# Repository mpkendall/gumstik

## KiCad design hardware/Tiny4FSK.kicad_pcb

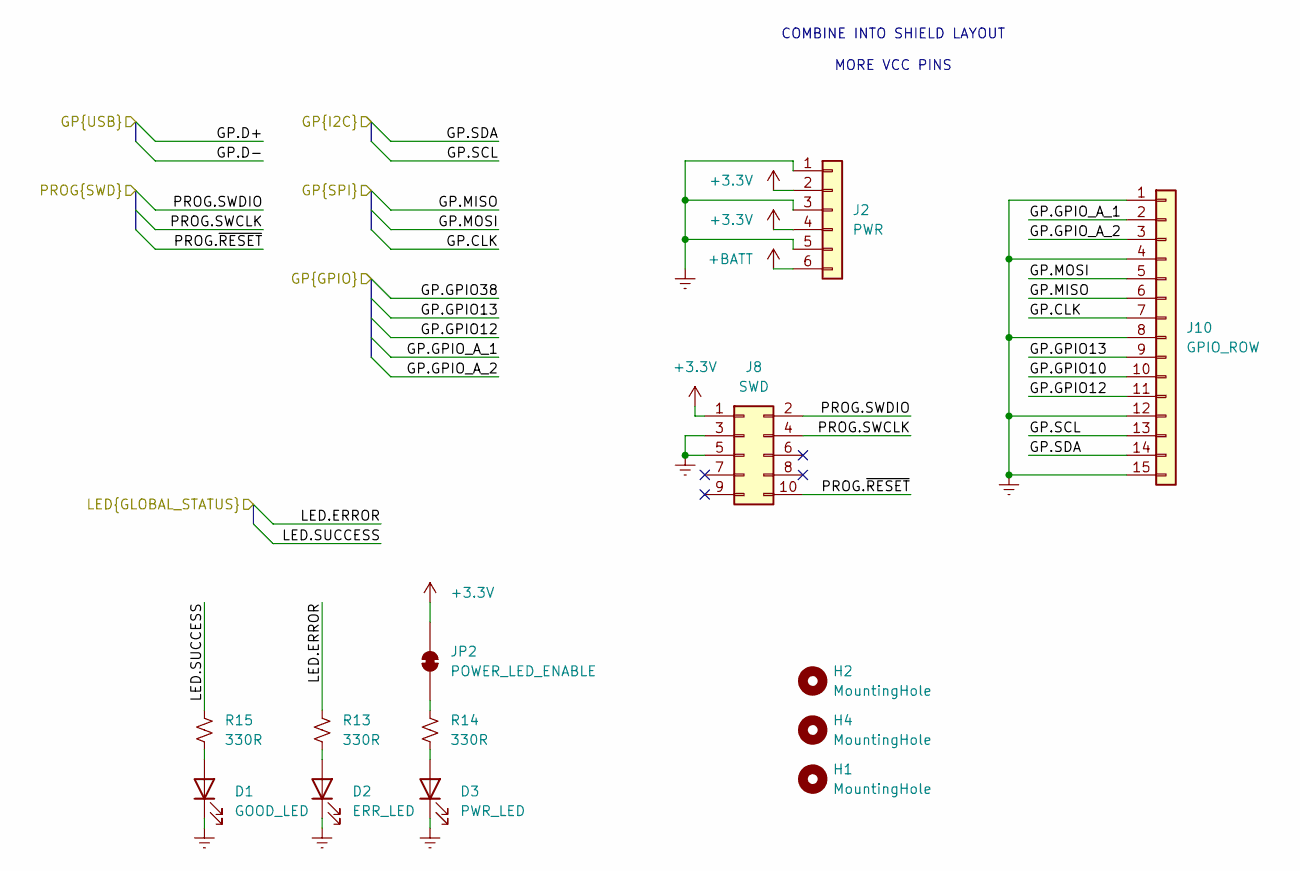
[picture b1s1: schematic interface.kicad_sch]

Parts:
D1: GOOD_LED; LED_0603_1608Metric; LCSC C2297
D2: ERR_LED; LED_0603_1608Metric; LCSC C84256
D3: PWR_LED; LED_0603_1608Metric; LCSC C84256
H1, H2, H4: MountingHole; MountingHole_2.2mm_M2
J2: PWR; PinHeader_1x06_P2.54mm_Vertical
J8: SWD; Pogo_2x05_P1.27mm
J10: GPIO_ROW; PinHeader_1x15_P2.54mm_Vertical
JP2: POWER_LED_ENABLE; SolderJumper-2_P1.3mm_Bridged_RoundedPad1.0x1.5mm
R13, R14, R15: 330R; C_0402_1005Metric; LCSC C23138

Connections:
+3.3V: J2.2, J2.4, J8.1, JP2.2 (B); also elsewhere on the board
+BATT: J2.6; also elsewhere on the board
/interface/GP.CLK: J10.7; also elsewhere on the board
/interface/GP.GPIO10: J10.10; also elsewhere on the board
/interface/GP.GPIO12: J10.11; also elsewhere on the board
/interface/GP.GPIO13: J10.9; also elsewhere on the board
/interface/GP.GPIO_A_1: J10.2; also elsewhere on the board
/interface/GP.GPIO_A_2: J10.3; also elsewhere on the board
/interface/GP.MISO: J10.6; also elsewhere on the board
/interface/GP.MOSI: J10.5; also elsewhere on the board
/interface/GP.SCL: J10.13; also elsewhere on the board
/interface/GP.SDA: J10.14; also elsewhere on the board
/interface/LED.ERROR: R13.1; also elsewhere on the board
/interface/LED.SUCCESS: R15.1; also elsewhere on the board
/interface/PROG.SWCLK: J8.4; also elsewhere on the board
/interface/PROG.SWDIO: J8.2; also elsewhere on the board
/interface/PROG.~RESET: J8.10; also elsewhere on the board
Earth: D1.1 (K), D2.1 (K), D3.1 (K), J2.1, J2.3, J2.5, J8.3, J8.5, J10.1, J10.4, J10.8, J10.12, J10.15; also elsewhere on the board
unnamed: D1.2 (A), R15.2
unnamed: D2.2 (A), R13.2
unnamed: D3.2 (A), R14.2
unnamed: JP2.1 (A), R14.1

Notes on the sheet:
COMBINE INTO SHIELD LAYOUT MORE VCC PINS

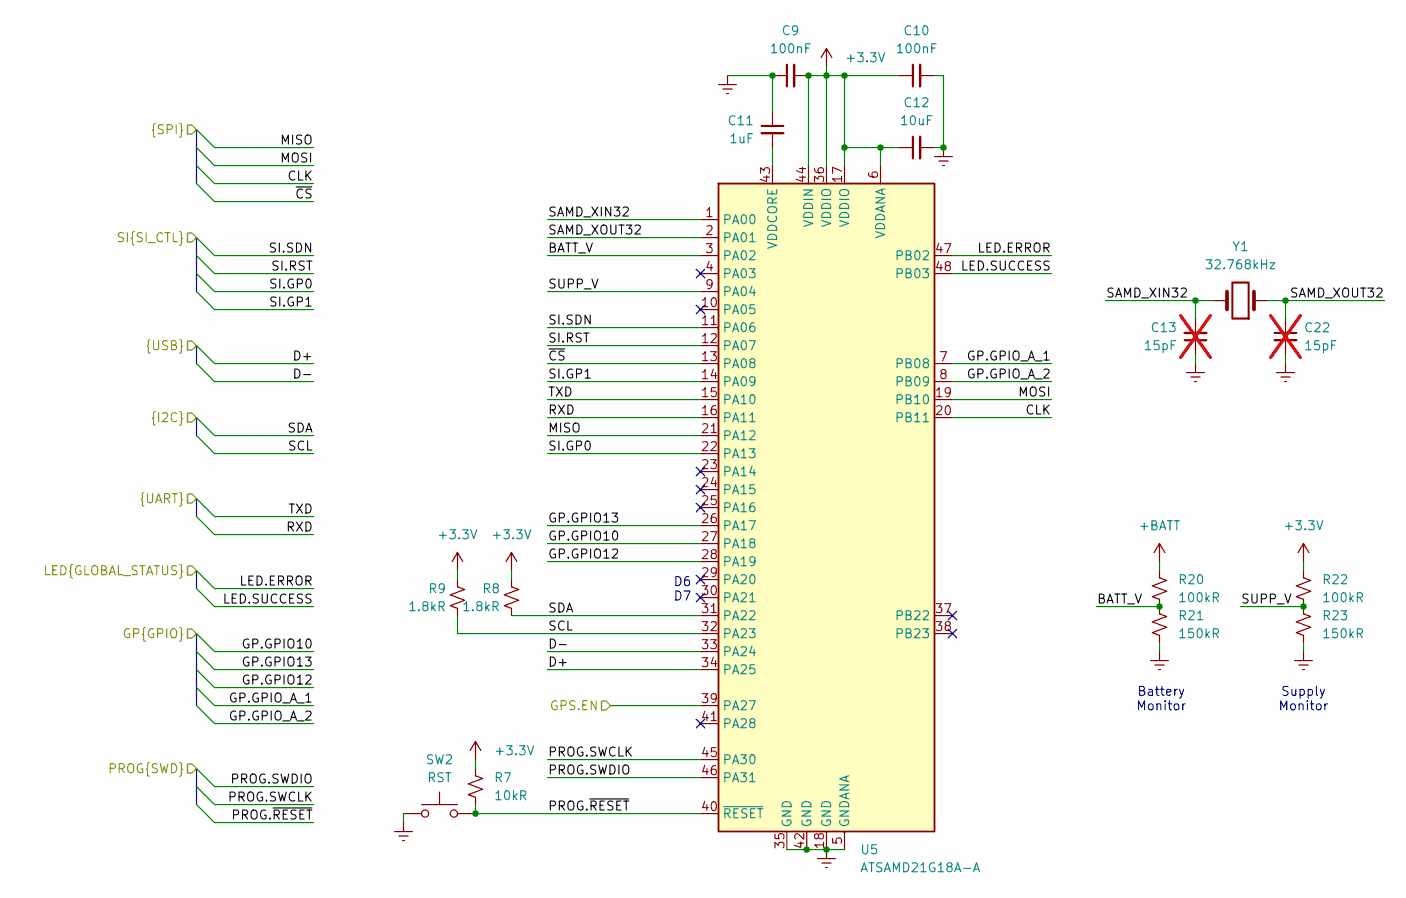
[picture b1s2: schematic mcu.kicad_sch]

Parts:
C9, C10: 100nF; C_0402_1005Metric; LCSC C1525
C11: 1uF; C_0402_1005Metric; LCSC C52923
C12: 10uF; C_0402_1005Metric; LCSC C19702
C13, C22: 15pF; C_0402_1005Metric; LCSC C1525; not fitted
R7: 10kR; R_0402_1005Metric; LCSC C25091
R8, R9: 1.8kR; R_0402_1005Metric; LCSC C4177
R20, R22: 100kR; C_0402_1005Metric; LCSC C26083
R21, R23: 150kR; C_0402_1005Metric; LCSC C26083
SW2: RST; SW_SPST_TS-1088-xR020; LCSC C2888954
U5: ATSAMD21G18A-A; TQFP-48_7x7mm_P0.5mm; LCSC C78624
Y1: 32.768kHz; Crystal_SMD_3215-2Pin_3.2x1.5mm; LCSC C32346

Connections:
+3.3V: C9.2, C10.1, C12.1, R7.2, R8.1, R9.1, R22.1, U5.6 (VDDANA), U5.17 (VDDIO), U5.36 (VDDIO), U5.44 (VDDIN); also elsewhere on the board
+BATT: R20.1; also elsewhere on the board
/interface/GP.CLK: U5.20 (PB11); also elsewhere on the board
/interface/GP.D+: U5.34 (PA25); also elsewhere on the board
/interface/GP.D-: U5.33 (PA24); also elsewhere on the board
/interface/GP.GPIO10: U5.27 (PA18); also elsewhere on the board
/interface/GP.GPIO12: U5.28 (PA19); also elsewhere on the board
/interface/GP.GPIO13: U5.26 (PA17); also elsewhere on the board
/interface/GP.GPIO_A_1: U5.7 (PB08); also elsewhere on the board
/interface/GP.GPIO_A_2: U5.8 (PB09); also elsewhere on the board
/interface/GP.MISO: U5.21 (PA12); also elsewhere on the board
/interface/GP.MOSI: U5.19 (PB10); also elsewhere on the board
/interface/GP.SCL: R9.2, U5.32 (PA23); also elsewhere on the board
/interface/GP.SDA: R8.2, U5.31 (PA22); also elsewhere on the board
/interface/GP.~CS: U5.13 (PA08); also elsewhere on the board
/interface/LED.ERROR: U5.47 (PB02); also elsewhere on the board
/interface/LED.SUCCESS: U5.48 (PB03); also elsewhere on the board
/interface/PROG.SWCLK: U5.45 (PA30); also elsewhere on the board
/interface/PROG.SWDIO: U5.46 (PA31); also elsewhere on the board
/interface/PROG.~RESET: R7.1, SW2.2, U5.40 (~RESET); also elsewhere on the board
/mcu/BATT_V: R20.2, R21.1, U5.3 (PA02)
/mcu/GPS.EN: U5.39 (PA27); also elsewhere on the board
/mcu/RXD: U5.16 (PA11); also elsewhere on the board
/mcu/SAMD_XIN32: C13.2, U5.1 (PA00), Y1.2
/mcu/SAMD_XOUT32: C22.1, U5.2 (PA01), Y1.1
/mcu/SI.GP0: U5.22 (PA13); also elsewhere on the board
/mcu/SI.GP1: U5.14 (PA09); also elsewhere on the board
/mcu/SI.RST: U5.12 (PA07); also elsewhere on the board
/mcu/SI.SDN: U5.11 (PA06); also elsewhere on the board
/mcu/SUPP_V: R22.2, R23.1, U5.9 (PA04)
/mcu/TXD: U5.15 (PA10); also elsewhere on the board
Earth: C9.1, C10.2, C11.1, C12.2, C13.1, C22.2, R21.2, R23.2, SW2.1, U5.5 (GNDANA), U5.18 (GND), U5.35 (GND), U5.42 (GND); also elsewhere on the board
unnamed: C11.2, U5.43 (VDDCORE)

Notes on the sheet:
Battery Monitor
Supply Monitor
D6 D7

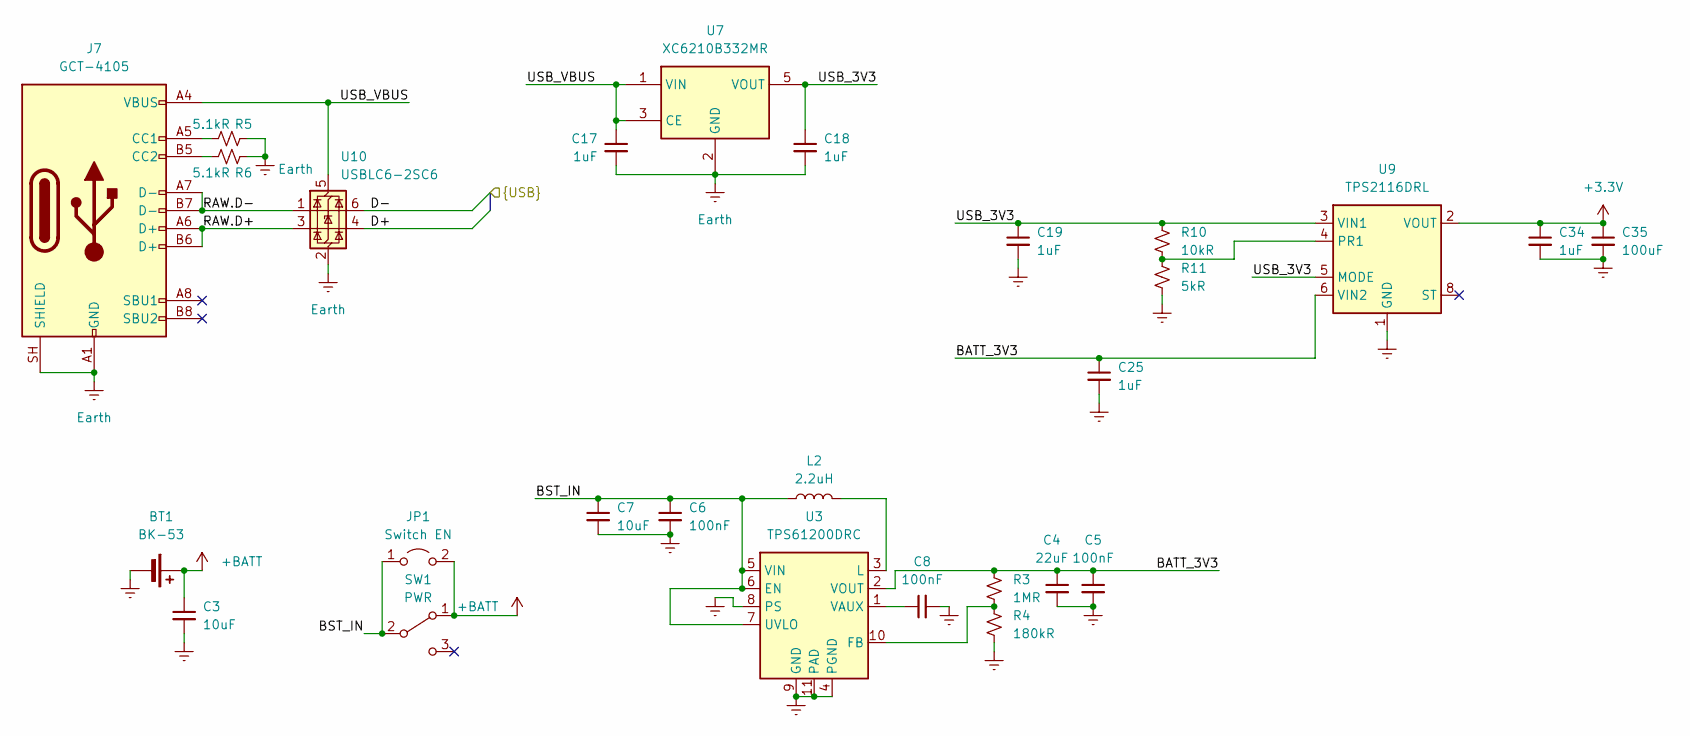
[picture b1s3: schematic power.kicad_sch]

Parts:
BT1: BK-53; BAT_BK-53
C3: 10uF; C_0402_1005Metric; LCSC C52923
C4: 22uF; C_0402_1005Metric; LCSC C59461
C5, C6, C8: 100nF; C_0402_1005Metric; LCSC C1525
C7: 10uF; C_0402_1005Metric; LCSC C19702
C17, C18, C19, C25, C34: 1uF; C_0402_1005Metric; LCSC C52923
C35: 100uF; C_0402_1005Metric; LCSC C52923
J7: GCT-4105; USB_C_Receptacle_GCT_USB4105-xx-A_16P_TopMnt_Horizontal; LCSC C2760486
JP1: Switch EN; SolderJumper-2_P1.3mm_Open_Pad1.0x1.5mm
L2: 2.2uH; L_Coilcraft_LPS3010; LCSC C2844756
R3: 1MR; R_0402_1005Metric; LCSC C26083
R4: 180kR; R_0402_1005Metric; LCSC C100276
R5, R6: 5.1kR; R_0402_1005Metric; LCSC C25905
R10: 10kR; R_0402_1005Metric
R11: 5kR; R_0402_1005Metric
SW1: PWR; SW_SPDT_PCM12; LCSC C963206
U3: TPS61200DRC; Texas_S-PVSON-N10_ThermalVias
U7: XC6210B332MR; SOT-23-5; LCSC C3021084
U9: TPS2116DRL; SOT-583-8; LCSC C3235557
U10: USBLC6-2SC6; SOT-23-6; LCSC C7519

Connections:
+3.3V: C34.1, C35.1, U9.2 (VOUT), U9.7 (VOUT); also elsewhere on the board
+BATT: BT1.1 (+), C3.1, JP1.2 (B), SW1.1 (A); also elsewhere on the board
/interface/GP.D+: U10.4 (I/O2); also elsewhere on the board
/interface/GP.D-: U10.6 (I/O1); also elsewhere on the board
/power/BATT_3V3: C4.1, C5.1, C25.1, R3.1, U3.2 (VOUT), U9.6 (VIN2)
/power/BST_IN: C6.1, C7.1, JP1.1 (A), L2.2, SW1.2 (B), U3.5 (VIN), U3.6 (EN), U3.7 (UVLO)
/power/RAW.D+: J7.A6 (D+), J7.B6 (D+), U10.3 (I/O2)
/power/RAW.D-: J7.A7 (D-), J7.B7 (D-), U10.1 (I/O1)
/power/USB_3V3: C18.1, C19.1, R10.2, U7.5 (VOUT), U9.3 (VIN1), U9.5 (MODE)
/power/USB_VBUS: C17.1, J7.A4 (VBUS), J7.A9 (VBUS), J7.B4 (VBUS), J7.B9 (VBUS), U7.1 (VIN), U7.3 (CE), U10.5 (VBUS)
Earth: BT1.2 (-), C3.2, C4.2, C5.2, C6.2, C7.2, C8.2, C17.2, C18.2, C19.2, C25.2, C34.2, C35.2, J7.A1 (GND), J7.A12 (GND), J7.B1 (GND), J7.B12 (GND), J7.SH (SHIELD), R4.2, R5.2, R6.2, R11.1, U3.4 (PGND), U3.8 (PS), U3.9 (GND), U3.11 (PAD), U7.2 (GND), U9.1 (GND), U10.2 (GND); also elsewhere on the board
unnamed: J7.A5 (CC1), R5.1
unnamed: J7.B5 (CC2), R6.1
unnamed: R3.2, R4.1, U3.10 (FB)
unnamed: L2.1, U3.3 (L)
unnamed: C8.1, U3.1 (VAUX)
unnamed: R10.1, R11.2, U9.4 (PR1)

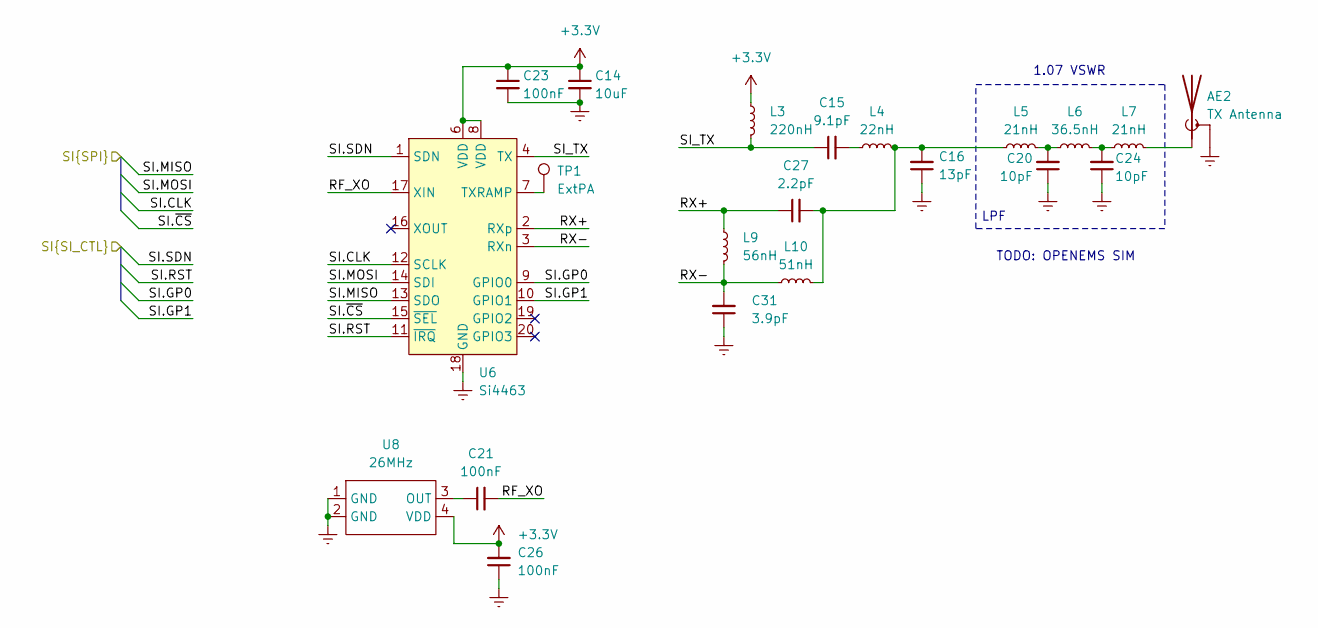
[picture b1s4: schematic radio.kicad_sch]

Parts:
AE2: TX Antenna; SMA_Samtec_SMA-J-P-H-ST-EM1_EdgeMount
C14: 10uF; C_0402_1005Metric; LCSC C19702
C15: 9.1pF; C_0402_1005Metric
C16: 13pF; C_0402_1005Metric
C20, C24: 10pF; C_0402_1005Metric
C21: 100nF; C_0402_1005Metric
C23, C26: 100nF; C_0402_1005Metric; LCSC C1525
C27: 2.2pF; C_0402_1005Metric
C31: 3.9pF; C_0402_1005Metric
L3: 220nH; L_0402_1005Metric
L4: 22nH; L_0402_1005Metric
L5, L7: 21nH; L_0402_1005Metric
L6: 36.5nH; L_0402_1005Metric
L9: 56nH; L_0402_1005Metric
L10: 51nH; L_0402_1005Metric
TP1: ExtPA; TestPoint_Pad_D1.0mm
U6: Si4463; QFN-20-1EP_4x4mm_P0.5mm_EP2.6x2.6mm_ThermalVias; LCSC C476202
U8: 26MHz; Crystal_SMD_2016-4Pin_2.0x1.6mm; LCSC C135223

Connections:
+3.3V: C14.1, C23.1, C26.2, L3.1, U6.6 (VDD), U6.8 (VDD), U8.4 (VDD); also elsewhere on the board
/interface/GP.CLK: U6.12 (SCLK); also elsewhere on the board
/interface/GP.MISO: U6.13 (SDO); also elsewhere on the board
/interface/GP.MOSI: U6.14 (SDI); also elsewhere on the board
/interface/GP.~CS: U6.15 (~SEL); also elsewhere on the board
/mcu/SI.GP0: U6.9 (GPIO0); also elsewhere on the board
/mcu/SI.GP1: U6.10 (GPIO1); also elsewhere on the board
/mcu/SI.RST: U6.11 (~IRQ); also elsewhere on the board
/mcu/SI.SDN: U6.1 (SDN); also elsewhere on the board
/radio/RF_XO: C21.2, U6.17 (XIN)
/radio/RX+: C27.1, L9.1, U6.2 (RXp)
/radio/RX-: C31.2, L9.2, L10.1, U6.3 (RXn)
/radio/SI_TX: C15.1, L3.2, U6.4 (TX)
Earth: AE2.2 (Shield), C14.2, C16.1, C20.1, C23.2, C24.1, C26.1, C31.1, U6.18 (GND), U6.21 (GND), U8.1 (GND), U8.2 (GND); also elsewhere on the board
unnamed: AE2.1 (RF), L7.2
unnamed: C15.2, L4.1
unnamed: C16.2, C27.2, L4.2, L5.1, L10.2
unnamed: C20.2, L5.2, L6.1
unnamed: C24.2, L6.2, L7.1
unnamed: TP1.1 (1_1), U6.7 (TXRAMP)
unnamed: C21.1, U8.3 (OUT)

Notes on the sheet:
1.07 VSWR
TODO: OPENEMS SIM
LPF

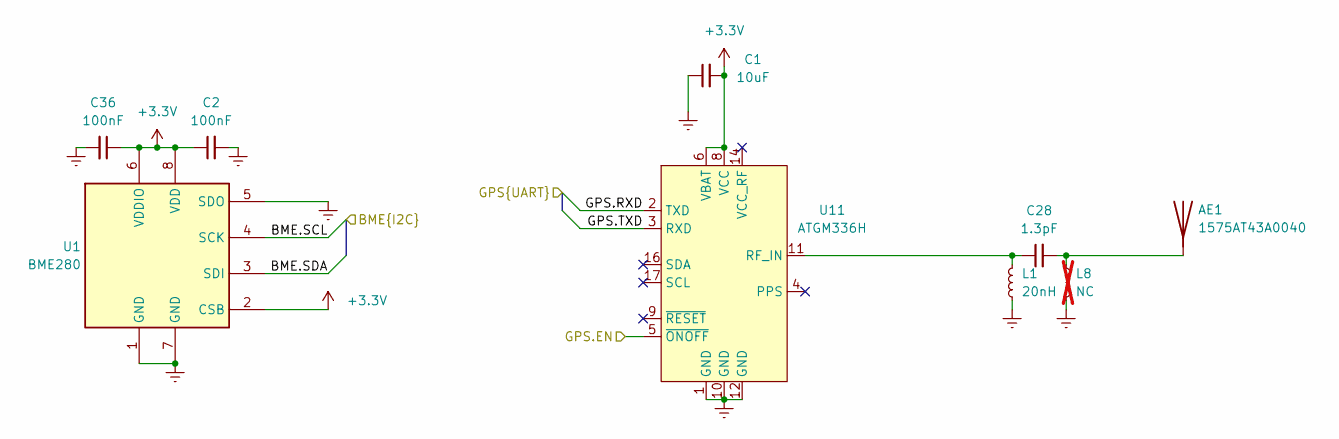
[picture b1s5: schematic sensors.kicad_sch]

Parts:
AE1: 1575AT43A0040; ANT_1575AT_JOT; LCSC C239243
C1: 10uF; C_0402_1005Metric; LCSC C19702
C2, C36: 100nF; C_0402_1005Metric; LCSC C52923
C28: 1.3pF; C_0402_1005Metric; LCSC C1525
L1: 20nH; C_0402_1005Metric; LCSC C307609
L8: NC; L_0402_1005Metric; LCSC C307609; not fitted
U1: BME280; Bosch_LGA-8_2.5x2.5mm_P0.65mm_ClockwisePinNumbering; LCSC C92489
U11: ATGM336H; ublox_MAX; LCSC C5117921

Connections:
+3.3V: C1.2, C2.1, C36.1, U1.2 (CSB), U1.6 (VDDIO), U1.8 (VDD), U11.6 (VBAT), U11.8 (VCC); also elsewhere on the board
/interface/GP.SCL: U1.4 (SCK); also elsewhere on the board
/interface/GP.SDA: U1.3 (SDI); also elsewhere on the board
/mcu/GPS.EN: U11.5 (~ONOFF); also elsewhere on the board
/mcu/RXD: U11.2 (TXD); also elsewhere on the board
/mcu/TXD: U11.3 (RXD); also elsewhere on the board
Earth: C1.1, C2.2, C36.2, L1.1, L8.2, U1.1 (GND), U1.5 (SDO), U1.7 (GND), U11.1 (GND), U11.10 (GND), U11.12 (GND); also elsewhere on the board
unnamed: AE1.1 (A_1), C28.2, L8.1
unnamed: C28.1, L1.2, U11.11 (RF_IN)

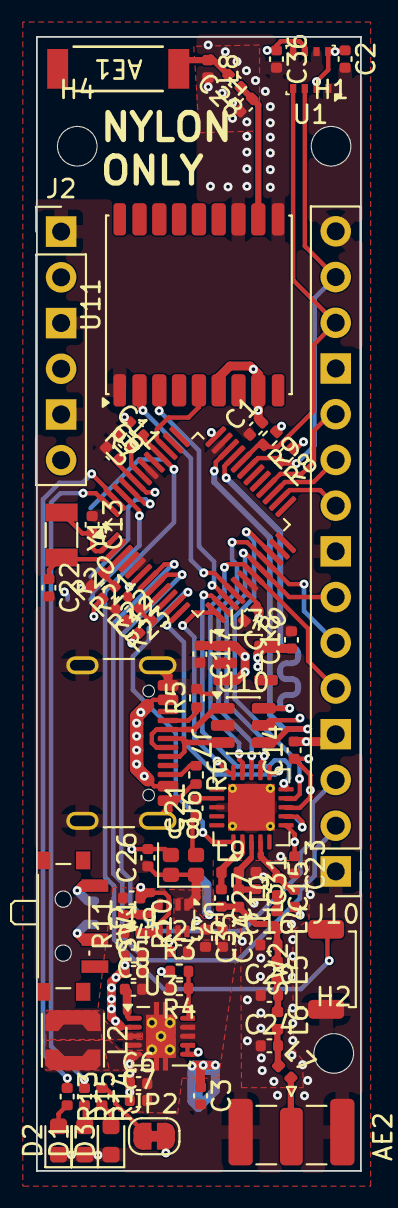
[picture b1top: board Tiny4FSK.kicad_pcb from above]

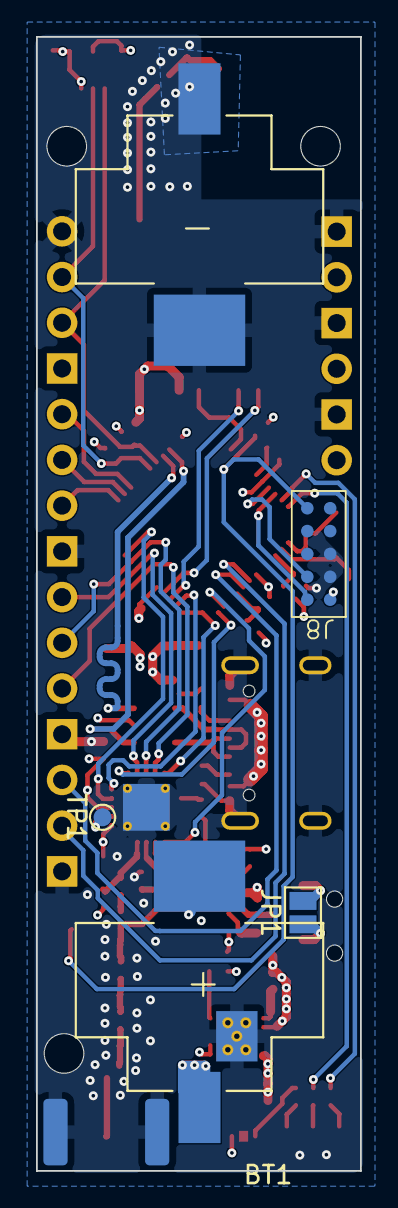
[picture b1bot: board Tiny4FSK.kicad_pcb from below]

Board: 4 copper layers, 18.0 x 63.0 mm, 86 parts (4 on the bottom side), 62 nets.
